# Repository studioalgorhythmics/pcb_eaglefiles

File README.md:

pcb_eaglefiles
==============

Some eagle files we are working on.

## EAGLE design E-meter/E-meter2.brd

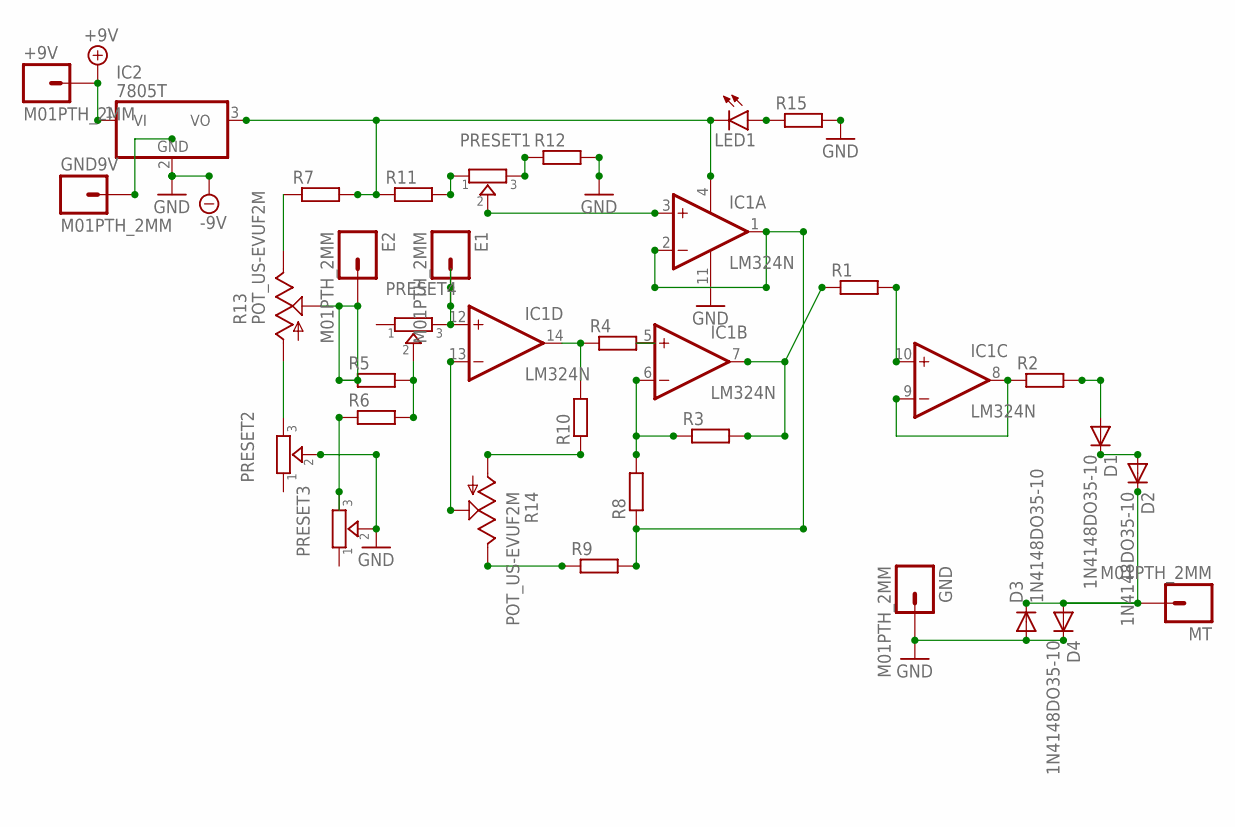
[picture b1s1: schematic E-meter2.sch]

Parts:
+9V: M01PTH_2MM; 1X01_2MM
D1, D2, D3, D4: 1N4148DO35-10; DO35-10
E1, E2: M01PTH_2MM; 1X01_2MM
GND, GND9V: M01PTH_2MM; 1X01_2MM
IC1: LM324N; DIL14
IC2: 7805T; TO220H
LED1: LED5MM
MT: M01PTH_2MM; 1X01_2MM
PRESET1, PRESET2, PRESET3, PRESET4: TRIMMER-3306F; TRIMMER_3306F
R1, R2, R3, R4, R5, R6, R7, R8, R9, R10, R11, R12, R15: R-EU_0207/10; 0207/10
R13, R14: POT_US-EVUF2M; POT_EVUFXM

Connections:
+9V: +9V.1, IC2.1 (VI)
GND: D3.A, D4.C, GND.1, IC1.11 (V-), IC2.2 (GND), PRESET2.2, PRESET3.2, R12.2, R15.2
unnamed: E2.1, R5.1, R13.2 (S)
unnamed: IC1.10 (+IN), R1.2
unnamed: IC1.6 (-IN), R3.1, R8.2
unnamed: IC1.1 (OUT), IC1.2 (-IN), R8.1, R9.2
unnamed: IC1.5 (+IN), R4.2
unnamed: IC1.14 (OUT), R4.1, R10.2
unnamed: IC1.8 (OUT), IC1.9 (-IN), R2.1
unnamed: D1.A, R2.2
unnamed: E1.1, IC1.12 (+IN), PRESET4.3
unnamed: D1.C, D2.A
unnamed: D2.C, D3.C, D4.A, MT.1
unnamed: IC1.3 (+IN), PRESET1.2
unnamed: PRESET1.1, R11.2
unnamed: IC1.4 (V+), IC2.3 (VO), LED1.K (C), R7.2, R11.1
unnamed: R7.1, R13.3 (E)
unnamed: PRESET1.3, R12.1
unnamed: R10.1, R14.1 (A)
unnamed: PRESET2.3, R13.1 (A)
unnamed: IC1.13 (-IN), R14.2 (S)
unnamed: R9.1, R14.3 (E)
unnamed: IC1.7 (OUT), R1.1, R3.2
unnamed: PRESET4.2, R5.2, R6.2
unnamed: PRESET3.3, R6.1
unnamed: LED1.A, R15.1

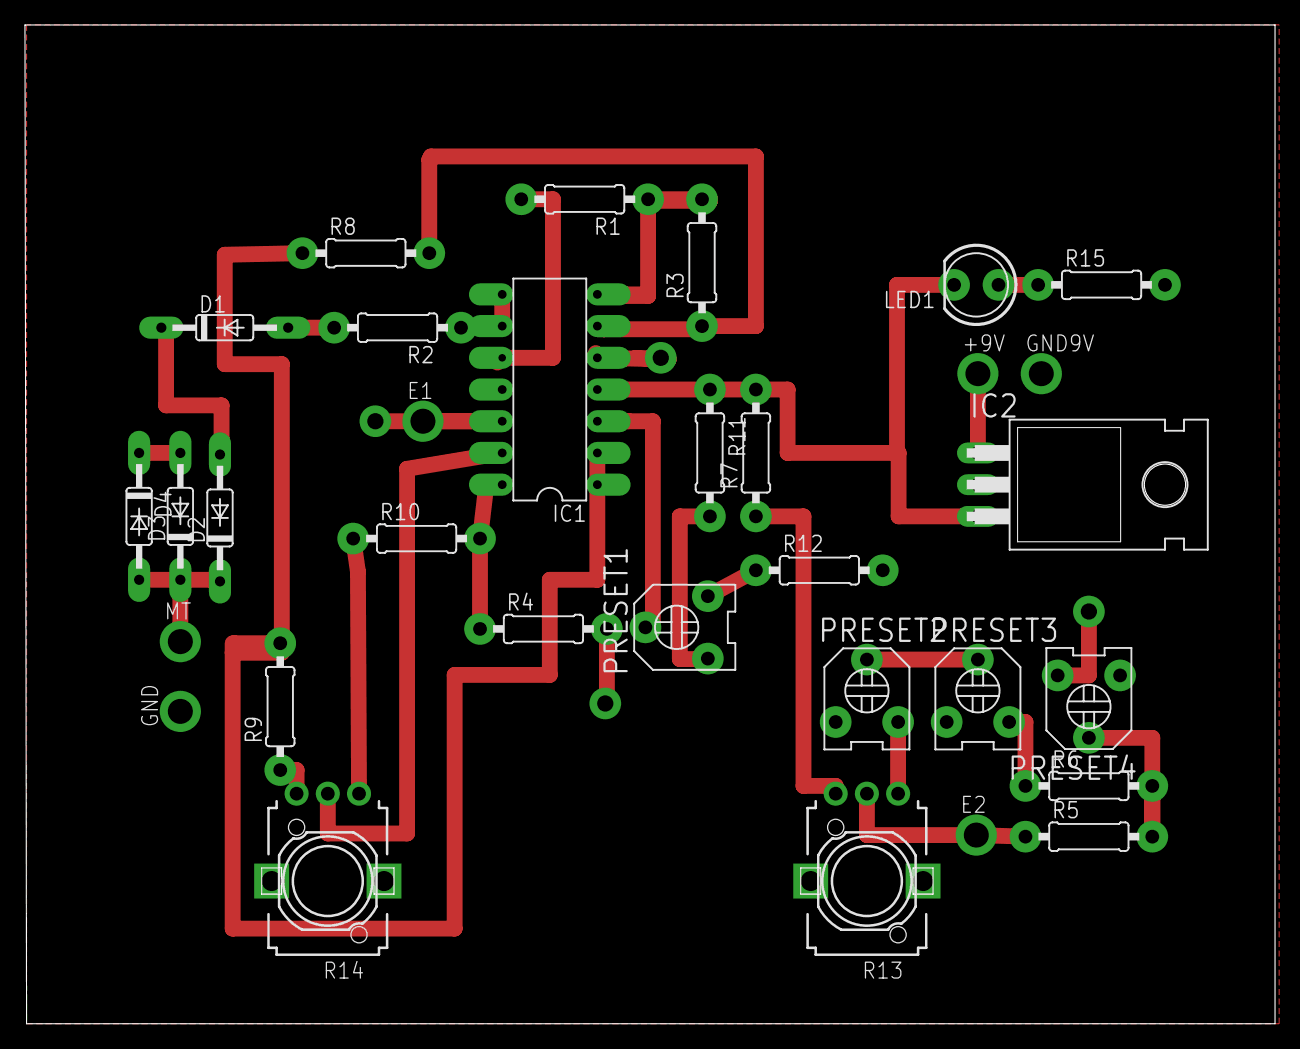
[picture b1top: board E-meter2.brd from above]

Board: 2 copper layers, 100.1 x 80.0 mm, 32 parts (0 on the bottom side), 26 nets.

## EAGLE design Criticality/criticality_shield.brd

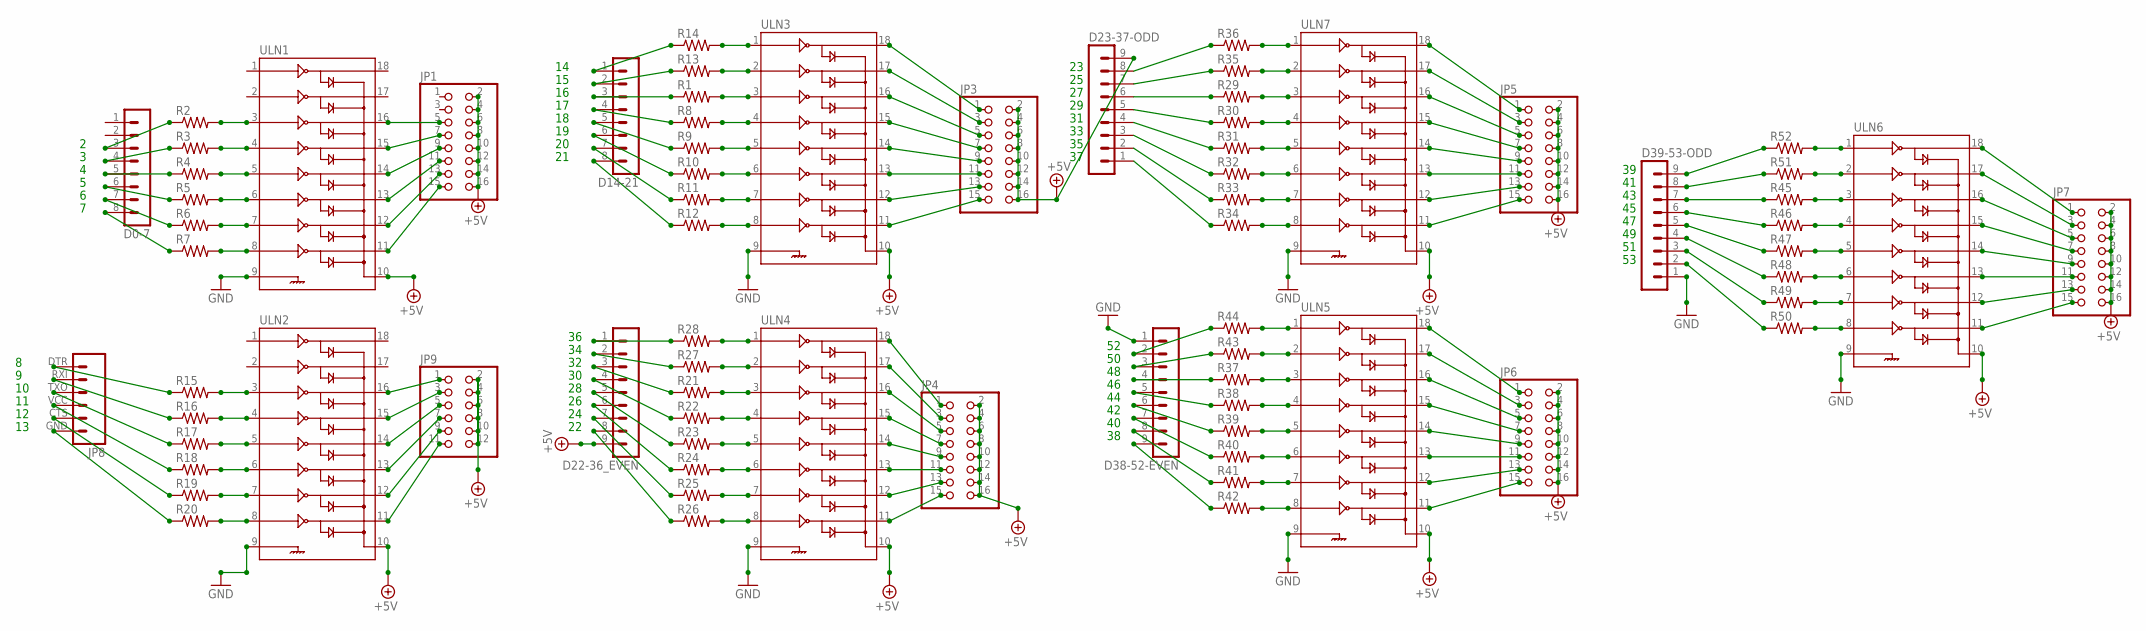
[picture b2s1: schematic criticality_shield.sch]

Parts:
D0-7, D14-21: MA08-1
D22-36_EVEN, D23-37-ODD, D38-52-EVEN, D39-53-ODD: MA09-1
JP1, JP3, JP4, JP5, JP6, JP7: PINHD-2X8; 2X08
JP8: M06SIP; 1X06
JP9: PINHD-2X6; 2X06
R1, R2, R3, R4, R5, R6, R7, R8, R9, R10, R11, R12, R13, R14, R15, R16, R17, R18, R19, R20, R21, R22, R23, R24, R25, R26, R27, R28, R29, R30, R31, R32, R33, R34, R35, R36, R37, R38, R39, R40, R41, R42, R43, R44, R45, R46, R47, R48, R49, R50, R51, R52: RESISTOR0603; 0603-RES
ULN1, ULN2, ULN3, ULN4, ULN5, ULN6, ULN7: ULN2803SOICW; SO18L

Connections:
+5V: D22-36_EVEN.9, D23-37-ODD.9, JP1.2, JP1.4, JP1.6, JP1.8, JP1.10, JP1.12, JP1.14, JP1.16, JP3.2, JP3.4, JP3.6, JP3.8, JP3.10, JP3.12, JP3.14, JP3.16, JP4.2, JP4.4, JP4.6, JP4.8, JP4.10, JP4.12, JP4.14, JP4.16, JP5.2, JP5.4, JP5.6, JP5.8, JP5.10, JP5.12, JP5.14, JP5.16, JP6.2, JP6.4, JP6.6, JP6.8, JP6.10, JP6.12, JP6.14, JP6.16, JP7.2, JP7.4, JP7.6, JP7.8, JP7.10, JP7.12, JP7.14, JP7.16, JP9.2, JP9.4, JP9.6, JP9.8, JP9.10, JP9.12, ULN1.10, ULN2.10, ULN3.10, ULN4.10, ULN5.10, ULN6.10, ULN7.10
GND: D38-52-EVEN.1, D39-53-ODD.1, ULN1.9, ULN2.9, ULN3.9, ULN4.9, ULN5.9, ULN6.9, ULN7.9
unnamed: D0-7.3, R2.1
unnamed: D0-7.4, R3.1
unnamed: D0-7.5, R4.1
unnamed: D0-7.6, R5.1
unnamed: JP8.DTR (1), R15.1
unnamed: JP8.RXI (2), R16.1
unnamed: D0-7.7, R6.1
unnamed: D0-7.8, R7.1
unnamed: R13.2, ULN3.2
unnamed: R14.2, ULN3.1
unnamed: JP1.5, ULN1.16
unnamed: JP1.7, ULN1.15
unnamed: JP8.TXO (3), R17.1
unnamed: JP8.VCC (4), R18.1
unnamed: JP8.CTS (5), R19.1
unnamed: JP8.GND (6), R20.1
unnamed: JP9.1, ULN2.16
unnamed: JP9.3, ULN2.15
unnamed: D14-21.1, R14.1
unnamed: D14-21.2, R13.1
unnamed: D14-21.3, R1.1
unnamed: D14-21.4, R8.1
unnamed: JP9.5, ULN2.14
unnamed: JP9.7, ULN2.13
unnamed: JP9.9, ULN2.12
unnamed: D14-21.5, R9.1
unnamed: D14-21.6, R10.1
unnamed: JP1.13, ULN1.12
unnamed: JP1.15, ULN1.11
unnamed: D14-21.7, R11.1
unnamed: D14-21.8, R12.1
unnamed: JP3.1, ULN3.18
unnamed: JP3.3, ULN3.17
unnamed: R26.2, ULN4.8
unnamed: R25.2, ULN4.7
unnamed: R12.2, ULN3.8
unnamed: R11.2, ULN3.7
unnamed: R24.2, ULN4.6
unnamed: R23.2, ULN4.5
unnamed: R22.2, ULN4.4
unnamed: R21.2, ULN4.3
unnamed: R10.2, ULN3.6
unnamed: R9.2, ULN3.5
unnamed: R27.2, ULN4.2
unnamed: R28.2, ULN4.1
unnamed: D22-36_EVEN.1, R28.1
unnamed: D22-36_EVEN.2, R27.1
unnamed: D22-36_EVEN.3, R21.1
unnamed: D22-36_EVEN.4, R22.1
unnamed: R34.2, ULN7.8
unnamed: R33.2, ULN7.7
unnamed: D22-36_EVEN.5, R23.1
unnamed: D22-36_EVEN.6, R24.1
unnamed: D22-36_EVEN.7, R25.1
unnamed: D22-36_EVEN.8, R26.1
unnamed: R32.2, ULN7.6
unnamed: R31.2, ULN7.5
unnamed: R30.2, ULN7.4
unnamed: R29.2, ULN7.3
unnamed: R35.2, ULN7.2
unnamed: R36.2, ULN7.1
unnamed: D23-37-ODD.8, R36.1
unnamed: D23-37-ODD.7, R35.1
unnamed: D23-37-ODD.6, R29.1
unnamed: JP1.9, ULN1.14
unnamed: JP1.11, ULN1.13
unnamed: D23-37-ODD.5, R30.1
unnamed: D23-37-ODD.4, R31.1
unnamed: R42.2, ULN5.8
unnamed: R41.2, ULN5.7
unnamed: R40.2, ULN5.6
unnamed: R39.2, ULN5.5
unnamed: R38.2, ULN5.4
unnamed: R37.2, ULN5.3
unnamed: R43.2, ULN5.2
unnamed: R44.2, ULN5.1
unnamed: D38-52-EVEN.2, R44.1
unnamed: D38-52-EVEN.3, R43.1
unnamed: D38-52-EVEN.4, R37.1
unnamed: D38-52-EVEN.5, R38.1
unnamed: D23-37-ODD.3, R32.1
unnamed: D23-37-ODD.2, R33.1
unnamed: D23-37-ODD.1, R34.1
unnamed: D38-52-EVEN.6, R39.1
unnamed: D38-52-EVEN.7, R40.1
unnamed: D38-52-EVEN.8, R41.1
unnamed: D38-52-EVEN.9, R42.1
unnamed: R50.2, ULN6.8
unnamed: R49.2, ULN6.7
unnamed: R48.2, ULN6.6
unnamed: R47.2, ULN6.5
unnamed: R46.2, ULN6.4
unnamed: R45.2, ULN6.3
unnamed: R51.2, ULN6.2
unnamed: R52.2, ULN6.1
unnamed: D39-53-ODD.9, R52.1
unnamed: D39-53-ODD.8, R51.1
unnamed: D39-53-ODD.7, R45.1
unnamed: D39-53-ODD.6, R46.1
unnamed: D39-53-ODD.5, R47.1
unnamed: D39-53-ODD.4, R48.1
unnamed: D39-53-ODD.3, R49.1
unnamed: D39-53-ODD.2, R50.1
unnamed: R7.2, ULN1.8
unnamed: R6.2, ULN1.7
unnamed: R5.2, ULN1.6
unnamed: R4.2, ULN1.5
unnamed: R3.2, ULN1.4
unnamed: R2.2, ULN1.3
unnamed: R8.2, ULN3.4
unnamed: R1.2, ULN3.3
unnamed: JP4.1, ULN4.18
unnamed: JP4.3, ULN4.17
unnamed: JP4.5, ULN4.16
unnamed: JP4.7, ULN4.15
unnamed: JP4.9, ULN4.14
unnamed: JP4.11, ULN4.13
unnamed: JP4.13, ULN4.12
unnamed: JP4.15, ULN4.11
unnamed: JP9.11, ULN2.11
unnamed: JP5.1, ULN7.18
unnamed: JP5.3, ULN7.17
unnamed: JP5.5, ULN7.16
unnamed: JP5.7, ULN7.15
unnamed: JP5.9, ULN7.14
unnamed: JP3.5, ULN3.16
unnamed: JP3.7, ULN3.15
unnamed: JP3.9, ULN3.14
unnamed: JP3.11, ULN3.13
unnamed: JP3.13, ULN3.12
unnamed: JP3.15, ULN3.11
unnamed: R20.2, ULN2.8
unnamed: R19.2, ULN2.7
unnamed: JP7.1, ULN6.18
unnamed: JP7.3, ULN6.17
unnamed: JP7.5, ULN6.16
unnamed: JP7.7, ULN6.15
unnamed: JP7.9, ULN6.14
unnamed: JP7.11, ULN6.13
unnamed: JP7.13, ULN6.12
unnamed: JP7.15, ULN6.11
unnamed: JP5.11, ULN7.13
unnamed: JP5.13, ULN7.12
unnamed: JP5.15, ULN7.11
unnamed: JP6.1, ULN5.18
unnamed: JP6.3, ULN5.17
unnamed: JP6.5, ULN5.16
unnamed: JP6.7, ULN5.15
unnamed: JP6.9, ULN5.14
unnamed: R18.2, ULN2.6
unnamed: R17.2, ULN2.5
unnamed: R16.2, ULN2.4
unnamed: R15.2, ULN2.3
unnamed: JP6.11, ULN5.13
unnamed: JP6.13, ULN5.12
unnamed: JP6.15, ULN5.11

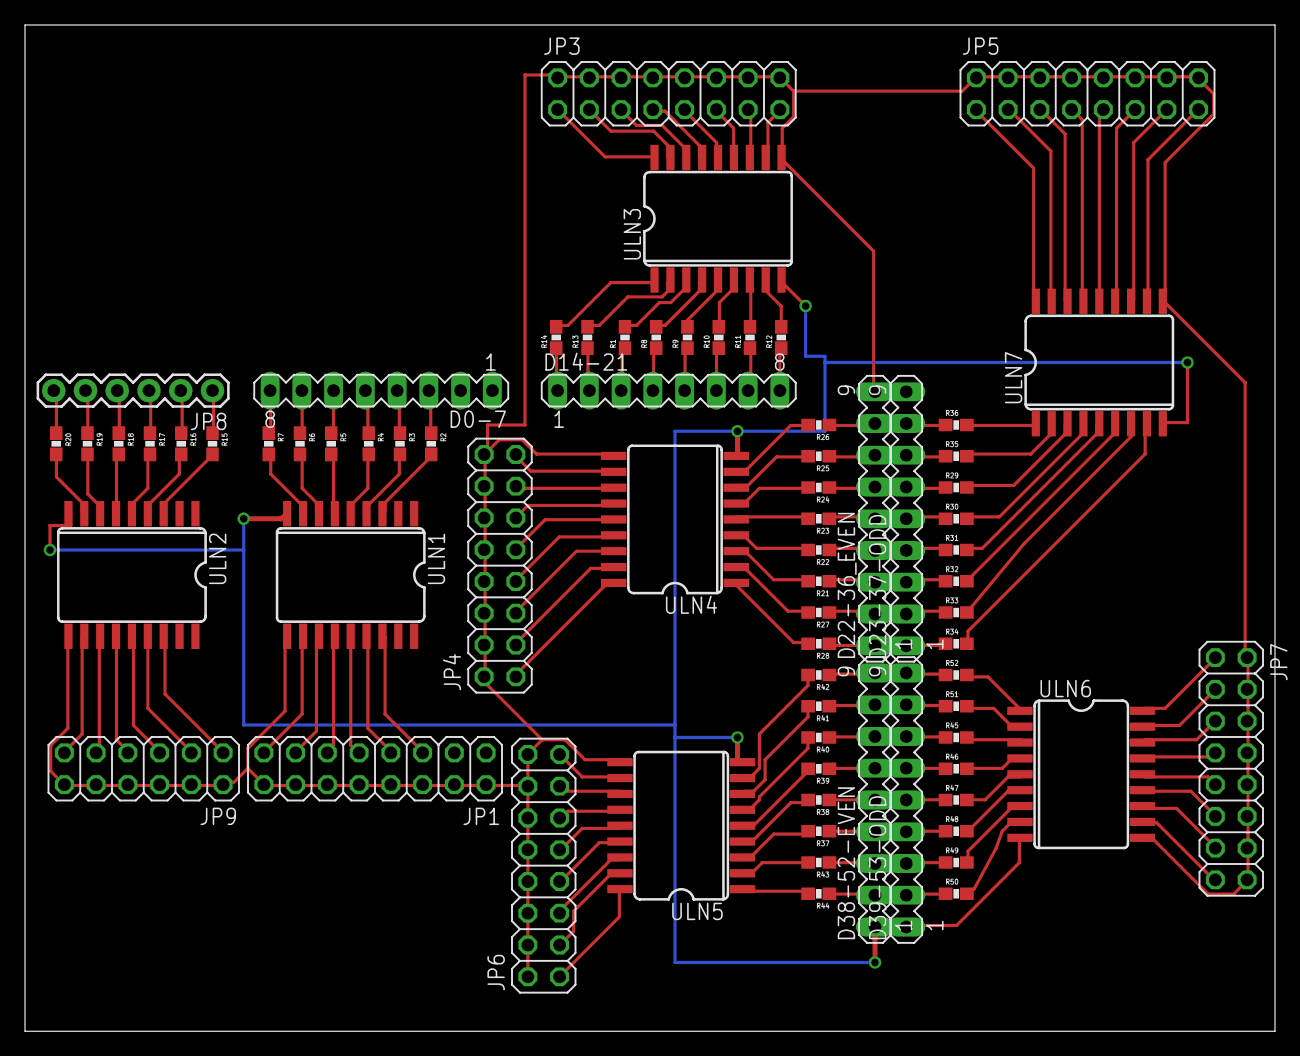
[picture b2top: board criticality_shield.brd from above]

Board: 2 copper layers, 100.0 x 80.5 mm, 73 parts (0 on the bottom side), 158 nets.

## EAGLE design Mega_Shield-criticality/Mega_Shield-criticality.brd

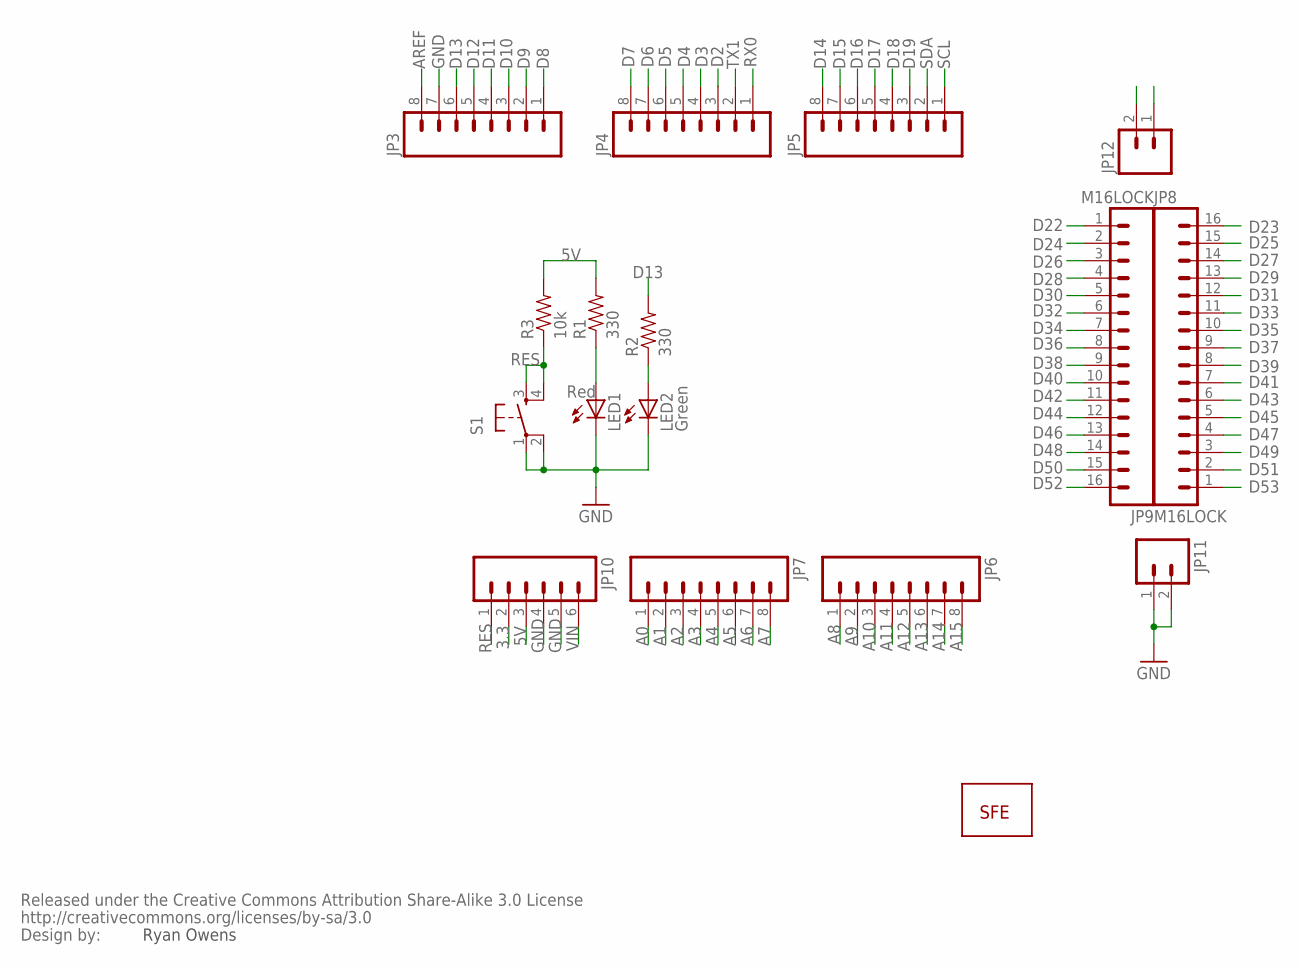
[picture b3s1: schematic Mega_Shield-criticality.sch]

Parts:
JP3, JP4, JP5, JP6, JP7: M08LOCK; 1X08_LOCK
JP8, JP9: M16LOCK; 1X16_LOCK
JP10: M06LOCK; 1X06_LOCK
JP11, JP12: M02LOCK; 1X02_LOCK
LED1: Red; LED5MM
LED2: Green; LED5MM
R1, R2: 330; AXIAL-0.3
R3: 10k; AXIAL-0.3
S1: TAC_SWITCHPTH; TACTILE-PTH
U$1: LOGO-SFENEW; SFE-NEW-WEBLOGO
U$2: CREATIVE_COMMONS

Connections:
3.3: JP10.2
5V: JP10.3, R1.P$2 (2), R3.P$2 (2)
5V@1: JP12.1, JP12.2
A0: JP7.1
A1: JP7.2
A2: JP7.3
A3: JP7.4
A4: JP7.5
A5: JP7.6
A6: JP7.7
A7: JP7.8
A8: JP6.1
A9: JP6.2
A10: JP6.3
A11: JP6.4
A12: JP6.5
A13: JP6.6
A14: JP6.7
A15: JP6.8
AREF: JP3.8
D2: JP4.3
D3: JP4.4
D4: JP4.5
D5: JP4.6
D6: JP4.7
D7: JP4.8
D8: JP3.1
D9: JP3.2
D10: JP3.3
D11: JP3.4
D12: JP3.5
D13: JP3.6, R2.P$2 (2)
D14: JP5.8
D15: JP5.7
D16: JP5.6
D17: JP5.5
D18: JP5.4
D19: JP5.3
D22: JP9.1
D23: JP8.16
D24: JP9.2
D25: JP8.15
D26: JP9.3
D27: JP8.14
D28: JP9.4
D29: JP8.13
D30: JP9.5
D31: JP8.12
D32: JP9.6
D33: JP8.11
D34: JP9.7
D35: JP8.10
D36: JP9.8
D37: JP8.9
D38: JP9.9
D39: JP8.8
D40: JP9.10
D41: JP8.7
D42: JP9.11
D43: JP8.6
D44: JP9.12
D45: JP8.5
D46: JP9.13
D47: JP8.4
D48: JP9.14
D49: JP8.3
D50: JP9.15
D51: JP8.2
D52: JP9.16
D53: JP8.1
GND: JP3.7, JP10.4, JP10.5, JP11.1, JP11.2, LED1.K (C), LED2.K (C), S1.1, S1.2
unnamed: LED1.A, R1.P$1 (1)
unnamed: LED2.A, R2.P$1 (1)
RES: JP10.1, R3.P$1 (1), S1.3, S1.4
RX0: JP4.1
SCL: JP5.1
SDA: JP5.2
TX1: JP4.2
VIN: JP10.6

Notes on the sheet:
Ryan Owens

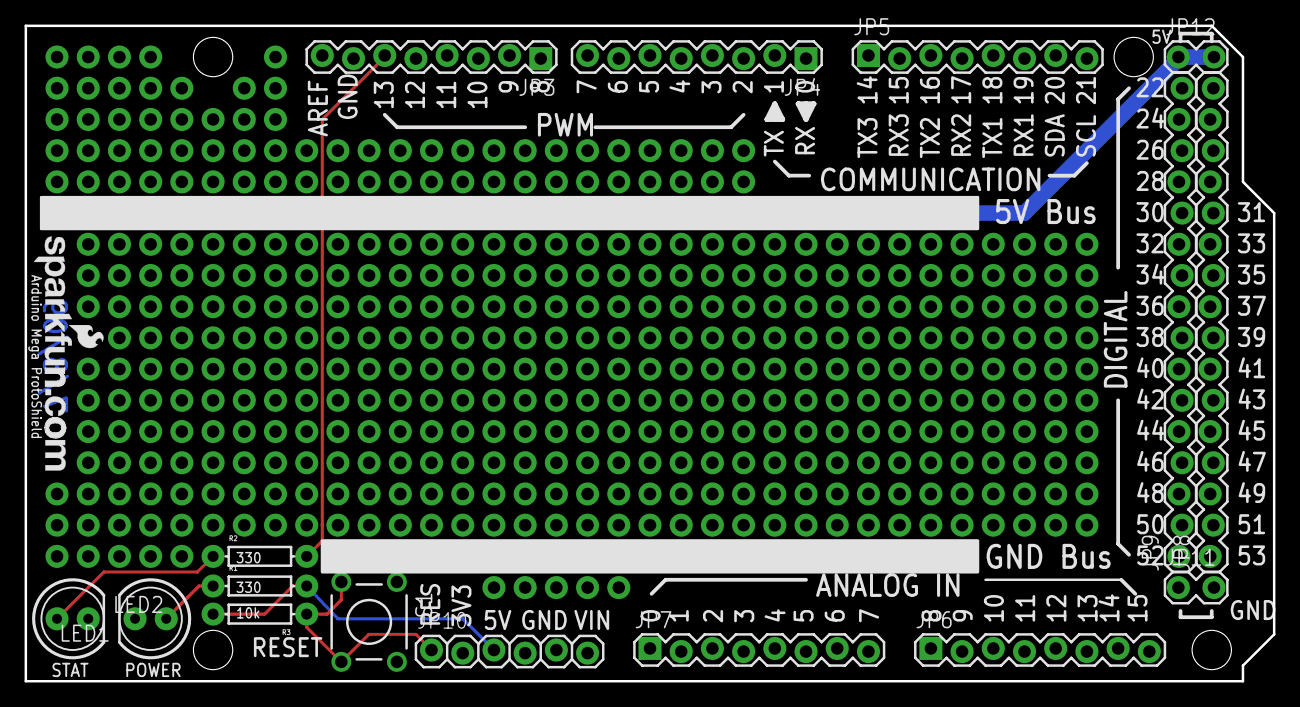
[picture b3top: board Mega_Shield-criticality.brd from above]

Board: 2 copper layers, 101.6 x 53.3 mm, 18 parts (0 on the bottom side), 7 nets.

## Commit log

2014-07-24 new files
2014-07-24 first attempt criticality-shield
2014-07-24 some small improvements
2014-07-24 added layers to "criticality"
2014-07-24 rearranged, all parts connected
2014-07-25 wired up everything, too messy..
2014-07-25 clean up, almost finished
2014-07-25 clean up
2014-07-25 deleted some files
2014-07-25 before autoroute, fitted to mega
2014-07-25 completely new version (SMD)
2014-07-25 SMD-version
2014-07-28 further improvements
2014-07-28 before groundplates
2014-07-29 final
2015-10-09 A new project E-Meter
2015-10-09 First version
2015-10-11 New Version
2015-10-16 small changes
2015-10-16 new layout
2015-10-16 another test
2015-10-20 new files last version, hand corrected pdf
2015-10-22 last adjustments cleaning of last_fin not mirrored with Illustrator
2015-11-21 cleaning up, pdfs with schematic, course material etc.

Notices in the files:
parts and their libraries:
SparkFun-PowerIC: Licensing: Creative Commons ShareAlike 4.0 International - https://creativecommons.org/licenses/by-sa/4.0
SparkFun: Released under the Creative Commons Attribution Share-Alike 3.0 License
SparkFun: http://creativecommons.org/licenses/by-sa/3.0
